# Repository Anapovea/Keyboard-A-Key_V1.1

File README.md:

# Keyboard-A-Key_V1.1
Keyboard designed using KiCAD

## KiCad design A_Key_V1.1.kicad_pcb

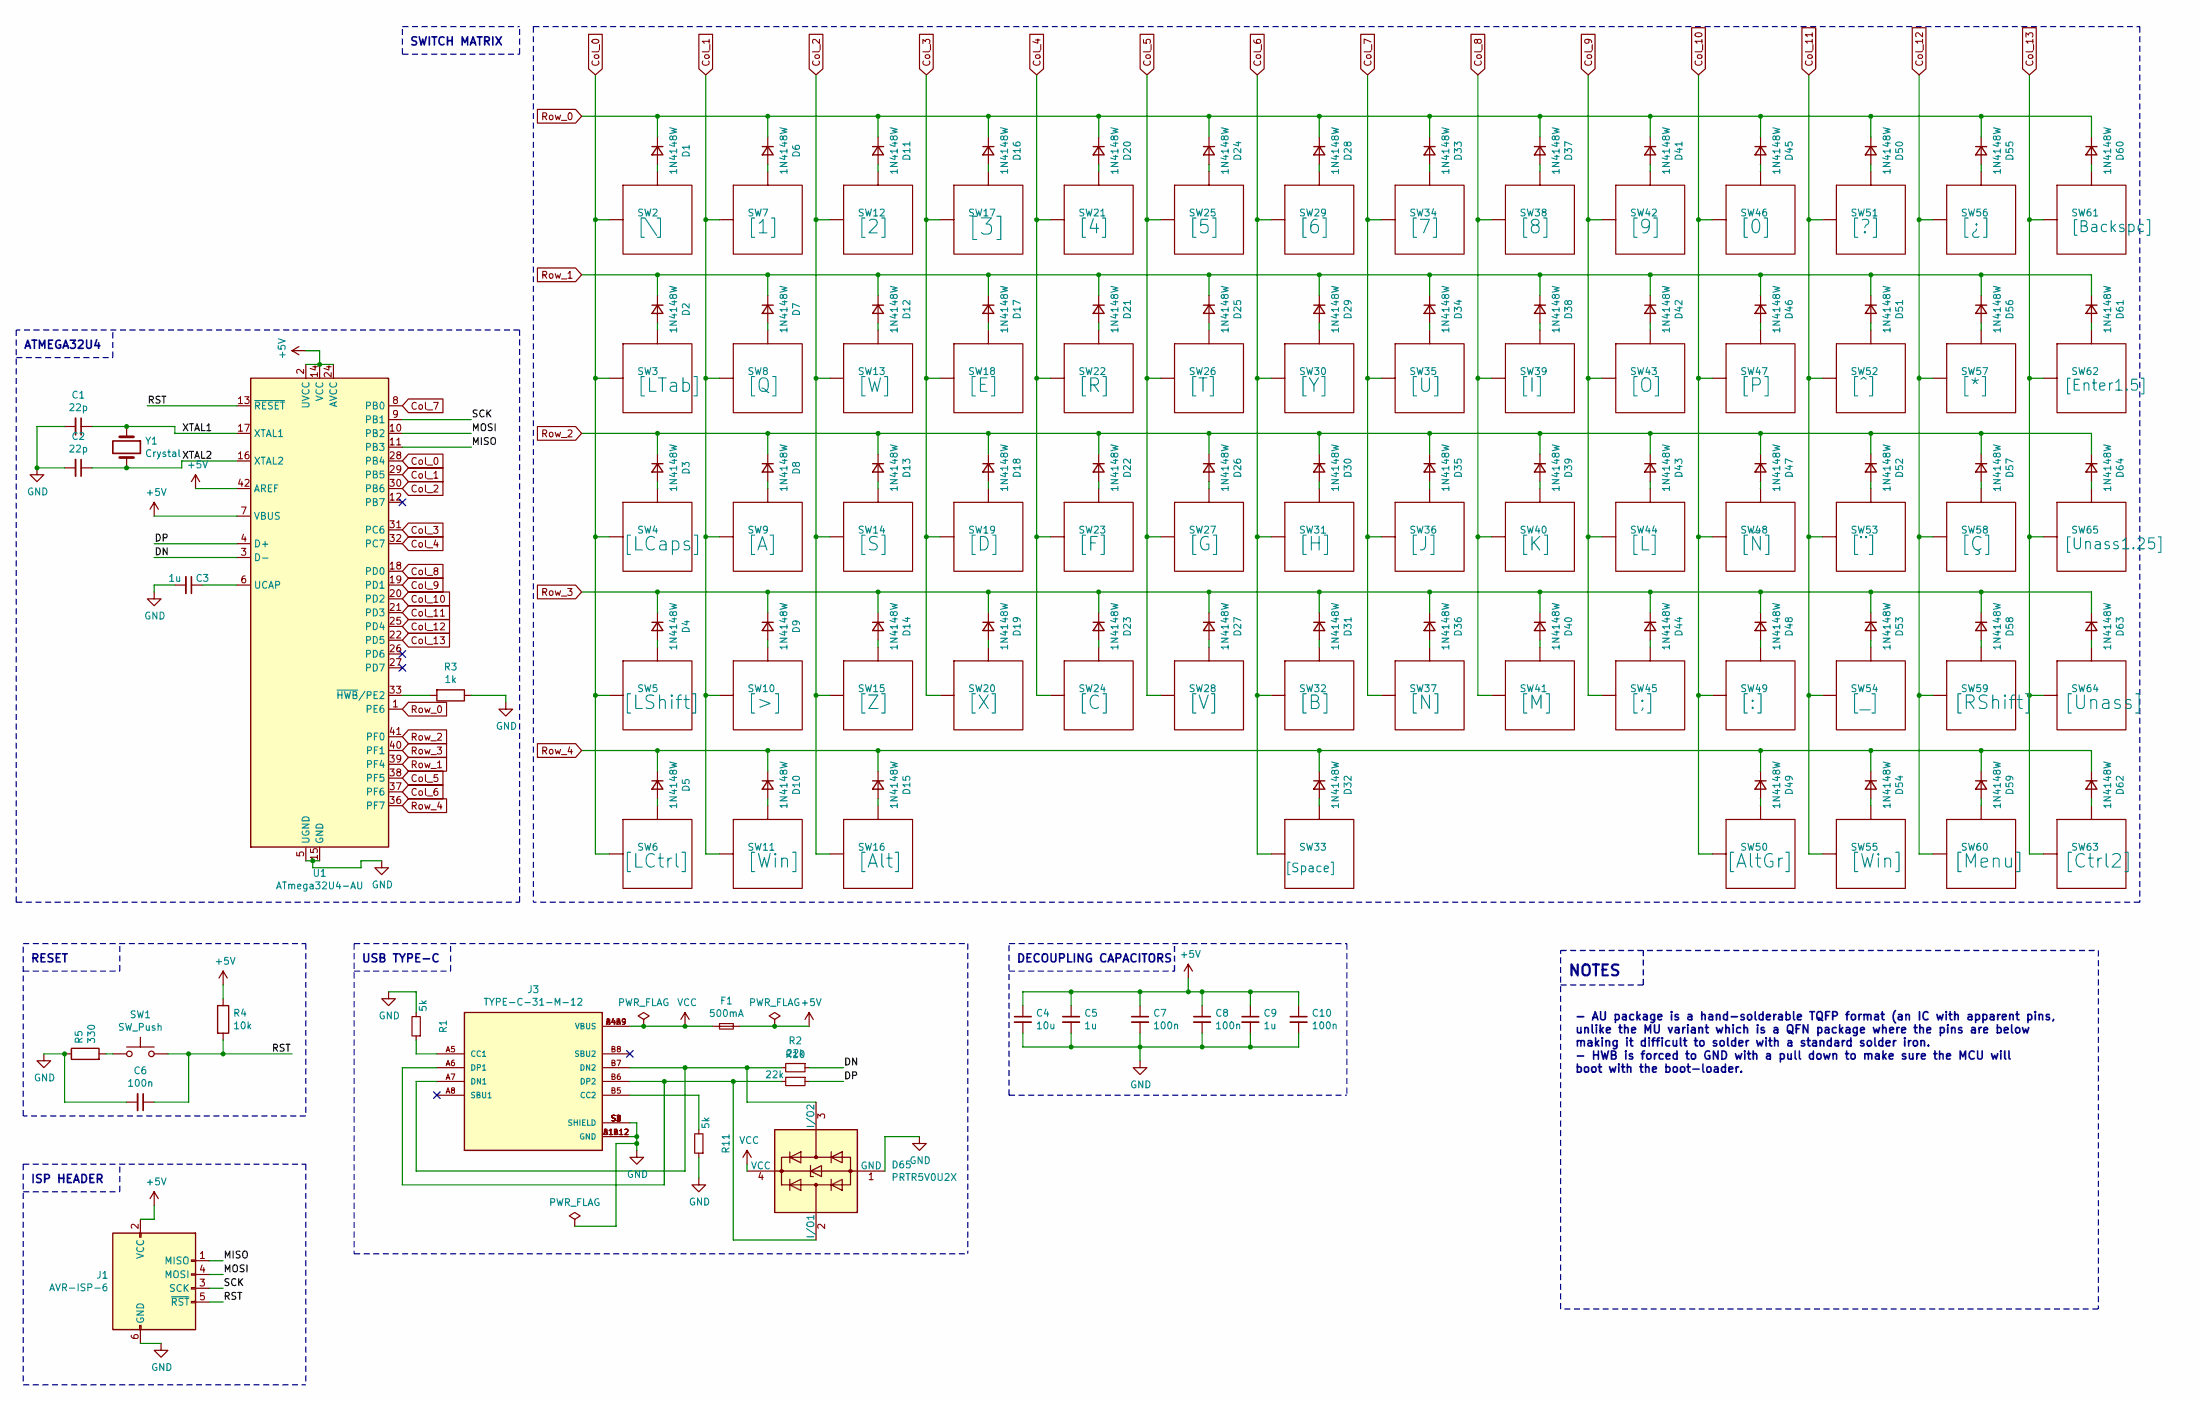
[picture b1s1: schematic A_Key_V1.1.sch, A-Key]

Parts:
C1, C2: 22p; C_0805_2012Metric_Pad1.18x1.45mm_HandSolder
C3, C5, C9: 1u; C_0805_2012Metric_Pad1.18x1.45mm_HandSolder
C4: 10u; C_0805_2012Metric_Pad1.18x1.45mm_HandSolder
C6, C7, C8, C10: 100n; C_0805_2012Metric_Pad1.18x1.45mm_HandSolder
D1, D2, D3, D4, D5, D6, D7, D8, D9, D10, D11, D12, D13, D14, D15, D16, D17, D18, D19, D20, D21, D22, D23, D24, D25, D26, D27, D28, D29, D30, D31, D32, D33, D34, D35, D36, D37, D38, D39, D40, D41, D42, D43, D44, D45, D46, D47, D48, D49, D50, D51, D52, D53, D54, D55, D56, D57, D58, D59, D60, D61, D62, D63, D64: 1N4148W; D_SOD-123
D65: PRTR5V0U2X; SOT-143
F1: 500mA; Fuse_1210_3225Metric_Pad1.42x2.65mm_HandSolder
J1: AVR-ISP-6; PinHeader_2x3_P2.54mm_Vertical
J3: TYPE-C-31-M-12; HRO_TYPE-C-31-M-12; PARTREV A
R1, R11: 5k; R_0805_2012Metric_Pad1.20x1.40mm_HandSolder
R2, R10: 22k; R_0805_2012Metric_Pad1.20x1.40mm_HandSolder
R3: 1k; R_0805_2012Metric_Pad1.20x1.40mm_HandSolder
R4: 10k; R_0805_2012Metric_Pad1.20x1.40mm_HandSolder
R5: 330; R_0805_2012Metric_Pad1.20x1.40mm_HandSolder
SW1: SW_Push; smdPushBtn
SW2: [\\]; MX100
SW3: [LTab]; MX150
SW4: [LCaps]; MX175
SW5: [LShift]; MX125
SW6: [LCtrl]; MX125
SW7: [1]; MX100
SW8: [Q]; MX100
SW9: [A]; MX100
SW10: [>]; MX100
SW11, SW55: [Win]; MX125
SW12: [2]; MX100
SW13: [W]; MX100
SW14: [S]; MX100
SW15: [Z]; MX100
SW16: [Alt]; MX125
SW17: [3]; MX100
SW18: [E]; MX100
SW19: [D]; MX100
SW20: [X]; MX100
SW21: [4]; MX100
SW22: [R]; MX100
SW23: [F]; MX100
SW24: [C]; MX100
SW25: [5]; MX100
SW26: [T]; MX100
SW27: [G]; MX100
SW28: [V]; MX100
SW29: [6]; MX100
SW30: [Y]; MX100
SW31: [H]; MX100
SW32: [B]; MX100
SW33: [Space]; MX625
SW34: [7]; MX100
SW35: [U]; MX100
SW36: [J]; MX100
SW37: [N]; MX100
SW38: [8]; MX100
SW39: [I]; MX100
SW40: [K]; MX100
SW41: [M]; MX100
SW42: [9]; MX100
SW43: [O]; MX100
SW44: [L]; MX100
SW45: [;]; MX100
SW46: [0]; MX100
SW47: [P]; MX100
SW48: [Ñ]; MX100
SW49: [:]; MX100
SW50: [AltGr]; MX125
SW51: [?]; MX100
SW52: [^]; MX100
SW53: [¨]; MX100
SW54: [_]; MX100
SW56: [¿]; MX100
SW57: [*]; MX100
SW58: [Ç]; MX100
SW59: [RShift]; MX150
SW60: [Menu]; MX125
SW61: [Backspc]; MX200
SW62: [Enter1.5]; MX150
SW63: [Ctrl2]; MX125
SW64: [Unass]; MX125
SW65: [Unass1.25]; MX125
U1: ATmega32U4-AU; TQFP-44_10x10mm_P0.8mm
Y1: Crystal; Crystal_SMD_5032-2Pin_5.0x3.2mm_HandSoldering

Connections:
+5V: C4.1, C5.1, C7.1, C8.1, C9.1, C10.1, F1.2, J1.2 (VCC), R4.1, U1.2 (UVCC), U1.7 (VBUS), U1.14 (VCC), U1.24 (AVCC), U1.34 (VCC), U1.42 (AREF), U1.44 (AVCC)
/DN: R2.1, U1.3 (D-)
/DP: R10.1, U1.4 (D+)
/MISO: J1.1 (MISO), U1.11 (PB3)
/MOSI: J1.4 (MOSI), U1.10 (PB2)
/RST: C6.1, J1.5 (~RST), R4.2, SW1.2, U1.13 (~RESET)
/SCK: J1.3 (SCK), U1.9 (PB1)
/XTAL1: C1.1, U1.17 (XTAL1), Y1.1
/XTAL2: C2.1, U1.16 (XTAL2), Y1.2
Col_0: SW2.1 (Col), SW3.1 (Col), SW4.1 (Col), SW5.1 (Col), SW6.1 (Col), U1.28 (PB4)
Col_1: SW7.1 (Col), SW8.1 (Col), SW9.1 (Col), SW10.1 (Col), SW11.1 (Col), U1.29 (PB5)
Col_2: SW12.1 (Col), SW13.1 (Col), SW14.1 (Col), SW15.1 (Col), SW16.1 (Col), U1.30 (PB6)
Col_3: SW17.1 (Col), SW18.1 (Col), SW19.1 (Col), SW20.1 (Col), U1.31 (PC6)
Col_4: SW21.1 (Col), SW22.1 (Col), SW23.1 (Col), SW24.1 (Col), U1.32 (PC7)
Col_5: SW25.1 (Col), SW26.1 (Col), SW27.1 (Col), SW28.1 (Col), U1.38 (PF5)
Col_6: SW29.1 (Col), SW30.1 (Col), SW31.1 (Col), SW32.1 (Col), SW33.1 (Col), U1.37 (PF6)
Col_7: SW34.1 (Col), SW35.1 (Col), SW36.1 (Col), SW37.1 (Col), U1.8 (PB0)
Col_8: SW38.1 (Col), SW39.1 (Col), SW40.1 (Col), SW41.1 (Col), U1.18 (PD0)
Col_9: SW42.1 (Col), SW43.1 (Col), SW44.1 (Col), SW45.1 (Col), U1.19 (PD1)
Col_10: SW46.1 (Col), SW47.1 (Col), SW48.1 (Col), SW49.1 (Col), SW50.1 (Col), U1.20 (PD2)
Col_11: SW51.1 (Col), SW52.1 (Col), SW53.1 (Col), SW54.1 (Col), SW55.1 (Col), U1.21 (PD3)
Col_12: SW56.1 (Col), SW57.1 (Col), SW58.1 (Col), SW59.1 (Col), SW60.1 (Col), U1.25 (PD4)
Col_13: SW61.1 (Col), SW62.1 (Col), SW63.1 (Col), SW64.1 (Col), SW65.1 (Col), U1.22 (PD5)
GND: C1.2, C2.2, C3.2, C4.2, C5.2, C6.2, C7.2, C8.2, C9.2, C10.2, D65.1 (GND), J1.6 (GND), J3.A1B12 (GND), J3.B1A12 (GND), J3.S1 (SHIELD), J3.S2 (SHIELD), J3.S3 (SHIELD), J3.S4 (SHIELD), R1.2, R3.1, R5.1, R11.1, U1.5 (UGND), U1.15 (GND), U1.23 (GND), U1.35 (GND), U1.43 (GND)
unnamed: C3.1, U1.6 (UCAP)
unnamed: D1.2 (A), SW2.2 (Row)
unnamed: D2.2 (A), SW3.2 (Row)
unnamed: D3.2 (A), SW4.2 (Row)
unnamed: D4.2 (A), SW5.2 (Row)
unnamed: D5.2 (A), SW6.2 (Row)
unnamed: D6.2 (A), SW7.2 (Row)
unnamed: D7.2 (A), SW8.2 (Row)
unnamed: D8.2 (A), SW9.2 (Row)
unnamed: D9.2 (A), SW10.2 (Row)
unnamed: D10.2 (A), SW11.2 (Row)
unnamed: D11.2 (A), SW12.2 (Row)
unnamed: D12.2 (A), SW13.2 (Row)
unnamed: D13.2 (A), SW14.2 (Row)
unnamed: D14.2 (A), SW15.2 (Row)
unnamed: D15.2 (A), SW16.2 (Row)
unnamed: D16.2 (A), SW17.2 (Row)
unnamed: D17.2 (A), SW18.2 (Row)
unnamed: D18.2 (A), SW19.2 (Row)
unnamed: D19.2 (A), SW20.2 (Row)
unnamed: D20.2 (A), SW21.2 (Row)
unnamed: D21.2 (A), SW22.2 (Row)
unnamed: D22.2 (A), SW23.2 (Row)
unnamed: D23.2 (A), SW24.2 (Row)
unnamed: D24.2 (A), SW25.2 (Row)
unnamed: D25.2 (A), SW26.2 (Row)
unnamed: D26.2 (A), SW27.2 (Row)
unnamed: D27.2 (A), SW28.2 (Row)
unnamed: D28.2 (A), SW29.2 (Row)
unnamed: D29.2 (A), SW30.2 (Row)
unnamed: D30.2 (A), SW31.2 (Row)
unnamed: D31.2 (A), SW32.2 (Row)
unnamed: D32.2 (A), SW33.2 (Row)
unnamed: D33.2 (A), SW34.2 (Row)
unnamed: D34.2 (A), SW35.2 (Row)
unnamed: D35.2 (A), SW36.2 (Row)
unnamed: D36.2 (A), SW37.2 (Row)
unnamed: D37.2 (A), SW38.2 (Row)
unnamed: D38.2 (A), SW39.2 (Row)
unnamed: D39.2 (A), SW40.2 (Row)
unnamed: D40.2 (A), SW41.2 (Row)
unnamed: D41.2 (A), SW42.2 (Row)
unnamed: D42.2 (A), SW43.2 (Row)
unnamed: D43.2 (A), SW44.2 (Row)
unnamed: D44.2 (A), SW45.2 (Row)
unnamed: D45.2 (A), SW46.2 (Row)
unnamed: D46.2 (A), SW47.2 (Row)
unnamed: D47.2 (A), SW48.2 (Row)
unnamed: D48.2 (A), SW49.2 (Row)
unnamed: D49.2 (A), SW50.2 (Row)
unnamed: D50.2 (A), SW51.2 (Row)
unnamed: D51.2 (A), SW52.2 (Row)
unnamed: D52.2 (A), SW53.2 (Row)
unnamed: D53.2 (A), SW54.2 (Row)
unnamed: D54.2 (A), SW55.2 (Row)
unnamed: D55.2 (A), SW56.2 (Row)
unnamed: D56.2 (A), SW57.2 (Row)
unnamed: D57.2 (A), SW58.2 (Row)
unnamed: D58.2 (A), SW59.2 (Row)
unnamed: D59.2 (A), SW60.2 (Row)
unnamed: D60.2 (A), SW61.2 (Row)
unnamed: D61.2 (A), SW62.2 (Row)
unnamed: D62.2 (A), SW63.2 (Row)
unnamed: D63.2 (A), SW64.2 (Row)
unnamed: D64.2 (A), SW65.2 (Row)
unnamed: D65.2 (I/O1), J3.A6 (DP1), J3.B6 (DP2), R10.2
unnamed: D65.3 (I/O2), J3.A7 (DN1), J3.B7 (DN2), R2.2
unnamed: J3.A5 (CC1), R1.1
unnamed: J3.B5 (CC2), R11.2
unnamed: R3.2, U1.33 (~HWB~/PE2)
unnamed: R5.2, SW1.1
Row_0: D1.1 (K), D6.1 (K), D11.1 (K), D16.1 (K), D20.1 (K), D24.1 (K), D28.1 (K), D33.1 (K), D37.1 (K), D41.1 (K), D45.1 (K), D50.1 (K), D55.1 (K), D60.1 (K), U1.1 (PE6)
Row_1: D2.1 (K), D7.1 (K), D12.1 (K), D17.1 (K), D21.1 (K), D25.1 (K), D29.1 (K), D34.1 (K), D38.1 (K), D42.1 (K), D46.1 (K), D51.1 (K), D56.1 (K), D61.1 (K), U1.39 (PF4)
Row_2: D3.1 (K), D8.1 (K), D13.1 (K), D18.1 (K), D22.1 (K), D26.1 (K), D30.1 (K), D35.1 (K), D39.1 (K), D43.1 (K), D47.1 (K), D52.1 (K), D57.1 (K), D64.1 (K), U1.41 (PF0)
Row_3: D4.1 (K), D9.1 (K), D14.1 (K), D19.1 (K), D23.1 (K), D27.1 (K), D31.1 (K), D36.1 (K), D40.1 (K), D44.1 (K), D48.1 (K), D53.1 (K), D58.1 (K), D63.1 (K), U1.40 (PF1)
Row_4: D5.1 (K), D10.1 (K), D15.1 (K), D32.1 (K), D49.1 (K), D54.1 (K), D59.1 (K), D62.1 (K), U1.36 (PF7)
VCC: D65.4 (VCC), F1.1, J3.A4B9 (VBUS), J3.B4A9 (VBUS)

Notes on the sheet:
USB TYPE-C
- AU package is a hand-solderable TQFP format (an IC with apparent pins, unlike the MU variant which is a QFN package where the pins are below making it difficult to solder with a standard solder iron. - HWB is forced to GND with a pull down to make sure the MCU will boot with the boot-loader.
DECOUPLING CAPACITORS
ATMEGA32U4
NOTES
RESET
ISP HEADER
SWITCH MATRIX

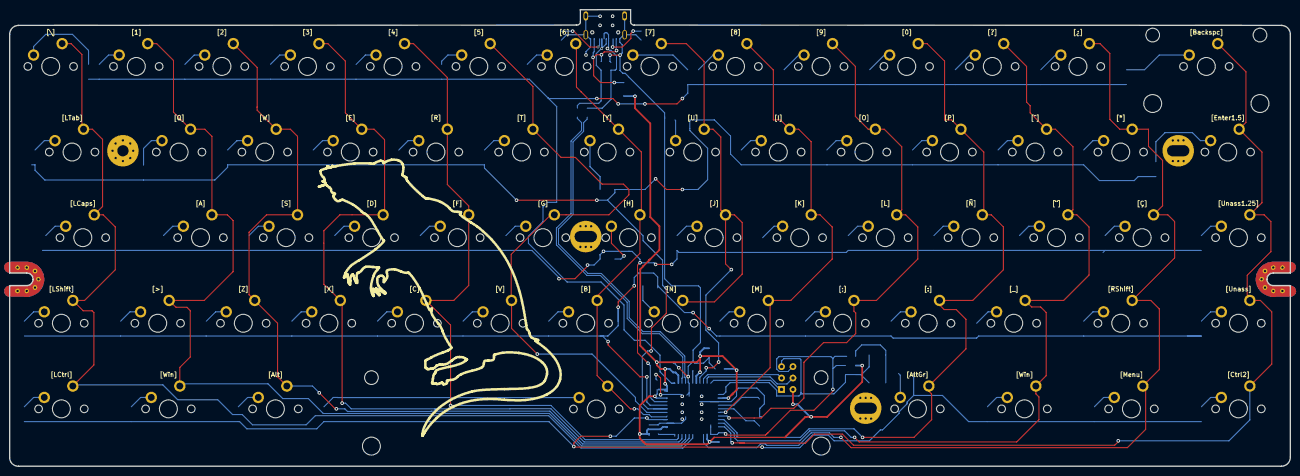
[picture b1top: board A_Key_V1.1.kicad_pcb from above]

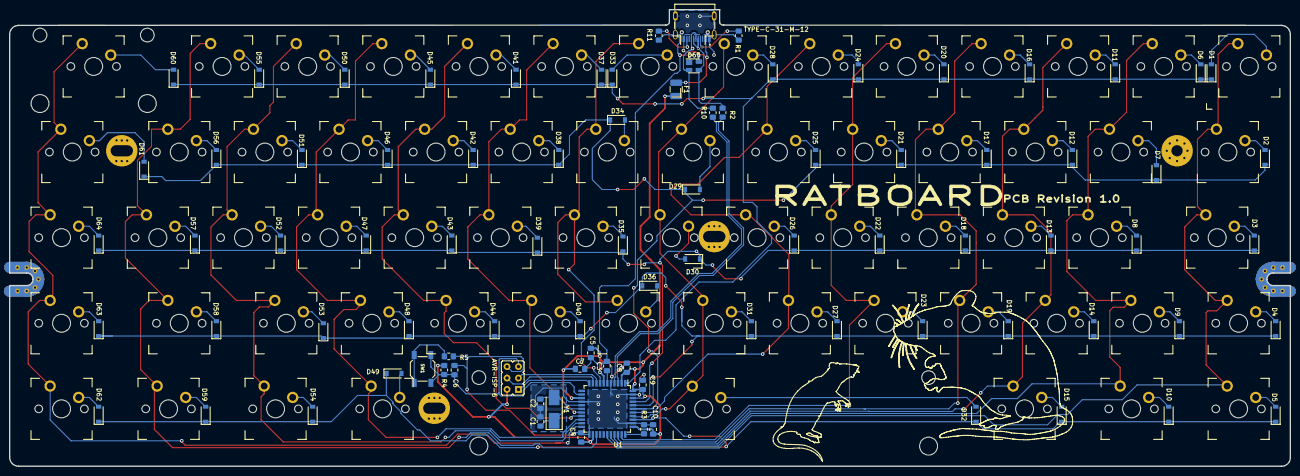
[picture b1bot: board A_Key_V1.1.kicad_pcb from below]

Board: 2 copper layers, 285.0 x 101.6 mm, 152 parts (152 on the bottom side), 101 nets.

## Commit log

2021-08-09 First
2021-08-10 PCB Layout almost finished
2021-08-10 Layout almost finished 2.0
2021-08-11 Almost finished (no revision yet)
2021-08-11 Almost finished
2021-08-12 GRAPHICS
2022-02-09 final
